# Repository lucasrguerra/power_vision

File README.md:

# Power Vision

## Descrição

O Power Vision é um projeto de código aberto destinado ao desenvolvimento de um analisador de qualidade da energia elétrica em tempo real utilizando um hardware de baixo custo com o microcontrolador ESP32-S3. Este analisador é capaz de medir e calcular uma variedade de parâmetros elétricos em sistemas monofásicos e trifásicos, fornecendo informações cruciais para análise e monitoramento de consumo de energia.

O projeto foi desenvolvido como Trabalho de Conclusão de Curso (TCC) do curso de Ciência da Computação da Universidade Federal Rural de Pernmabuco (UFRPE) e orientado pelo Prof. Dr. Abner Corrêa Barros. O projeto tem como objetivo principal a implementação de um analisador de energia elétrica de baixo custo e alta precisão, que possa ser utilizado em residências, empresas e indústrias para monitoramento e análise de consumo de energia.

## Funcionalidades

O Power Vision atualmente tem na teoria as seguintes funcionalidades:

- **Frequência (Hz)**: Medição da frequência do sistema.
- **Tensão True RMS (Vac)**: Medição precisa da tensão eficaz do sistema.
- **Corrente True RMS (A)**: Medição precisa da corrente eficaz do sistema.
- **Potência Aparente (kVA)**: Cálculo da potência aparente do sistema.
- **Distorção Harmônica Total (%)**: Avaliação da distorção harmônica no sistema.
- **Cosseno φ**: Cálculo do cosseno do ângulo de fase.
- **Fator de Potência (%)**: Determinação do fator de potência do sistema.
- **Potência Ativa (kW)**: Cálculo da potência ativa consumida pelo sistema.
- **Potência Reativa (kVAr)**: Cálculo da potência reativa do sistema.
- **Potência de Distorção (kVAD)**: Cálculo da potência de distorção do sistema.

## Limites de medição

Assim como qualquer equipamento de medição, o Power Vision possui limites de medição para cada parâmetro elétrico. Abaixo estão os limites de medição que este projeto visa alcançar:

### Frequência
O dispositivo possiu uma forma versátil de calcular a frequência, se mas o intervalo de leitura esperado é entre 45Hz e 60Hz.

### Tensão
O dispositivo é destinado a medições em sistemas residenciais, comerciais e industriais de pequeno e médio porte, para isso, o dispositivo conta com 4 níveis possíveis de tensão de fase (não confundir com tensão de linha, que é a tensão entre fases), sendo eles:

Nível 0 = 0-475Vac (Padrão 440V)  
Nível 1 = 0-440Vac (Padrão 380V)  
Nível 2 = 0-275Vac (Padrão 220V)  
Nível 3 = 0-175Vac (Padrão 127V)  

### Corrente
O dispositivo é destinado a medições em sistemas residenciais, comerciais e industriais de pequeno e médio porte, para isso, o dispositivo conta com 7 níveis possíveis de corrente, sendo eles:

Nível 0 = Até 1000A  
Nível 1 = Até 750A  
Nível 2 = Até 500A  
Nível 3 = Até 300A  
Nível 4 = Até 200A  
Nível 5 = Até 120A  
Nível 6 = Até 80A  

## Estrutura do Projeto

O projeto está organizado da seguinte forma:

- **[`src/`](./src/)**: Contém o código fonte principal do analisador de energia, que vai no Microcontrolador. (Em desenvolvimento 🛠️)

- **[`docs/`](./docs/)**: Documentação do projeto, incluindo manuais de usuário, especificações técnicas e outras informações relevantes.

- **[`theory/`](./theory/)**: Esta pasta contém implementações em Python das fórmulas utilizadas antes de serem integradas ao código principal do microcontrolador. (Sendo atualizado para a transformada Wavelet 🛠️)

- **[`boards/`](./boards/)**: Contém informações sobre as placas desenvolvidas para o projeto e os arquivos de fabricação no formato Gerber.

## Como Contribuir

Sinta-se à vontade para contribuir com o projeto! Você pode:

- Reportar problemas encontrados.
- Propor melhorias e novas funcionalidades.
- Enviar correções ou otimizações de código.
- Compartilhar suas experiências e ideias.

## Como Utilizar

Para utilizar o Power Vision, siga estas etapas:

1. Clone o repositório para o seu ambiente de desenvolvimento com o PlatformIO instalado.
2. Instale as dependências necessárias:
    (Atenção: Este projeto ainda não possui dependências)
3. Compile e carregue o código no seu ESP32-S3.
4. Monte o circuito conforme o esquemático disponível na pasta [`docs/`](./docs/).
4. Conecte o analisador de energia ao sistema que deseja analisar.
5. Inicie o analisador e visualize os resultados pela interface serial.

## Créditos

Este projeto foi criador por [Lucas Rayan](https://www.linkedin.com/in/lucasrguerra/) (vulgo "eu") e continua sendo mantido por ele.

## Agradecimentos

A minha mãe, que sempre lutou muito para que eu e minha irmã tivéssemos uma boa educação, e que sempre me apoiou em todas as minhas decisões. E que é sem dúvida a pessoa mais importante da minha vida.

Ao [Prof. Dr. Abner Corrêa Barros](https://www.linkedin.com/in/abner-barros-5b86409/), meu orientador, que sempre esteve disposto a ajudar e doar seu tempo e conhecimento para contribuir com o desenvolvimento do projeto.

A minha grande amiga e companheira de vida, [Vitória das Dores](https://www.linkedin.com/in/vitoria-das-dores/), que sempre esteve ao meu lado me apoiando e me ajudando a superar todos os desafios.

Ao meu grande amigo e grande Engenheiro Eletrônico, [João Pontes](https://www.linkedin.com/in/joão-victor-b-pontes-b37006116/), que sempre esteve disposto a ajudar e ouvir minhas ideias e dúvidas.

## Licença

Este projeto está licenciado sob a Licença MIT. Consulte o arquivo [LICENSE](./LICENSE) para obter mais detalhes.

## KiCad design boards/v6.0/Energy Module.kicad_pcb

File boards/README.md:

# Placas do projeto

## Descrição

Nesta pasta estão todos os arquivos das placas desenvolvidas para este projeto utilizando o software KiCAD. Dentre esses arquivos, estão o esquemático, o layout da placa e seus arquivos de fabricação no formato Gerber.

## Versões Disponíveis

- **[`v4.0`](./v4.0/)**: Essa é a 12ª versão da placa e no modelo SMT (Surface-Mount Technology).
- **[`v3.4`](./v3.4/)**: Essa é a 11ª versão da placa e no modelo SMT (Surface-Mount Technology).
- **[`v3.3`](./v3.3/)**: Essa é a 10ª versão da placa e no modelo THT (Through-Hole Technology).
- **[`v3.2`](./v3.2/)**: Essa é a 9ª versão da placa e no modelo THT (Through-Hole Technology).
- **[`v3.1`](./v3.1/)**: Essa é a 8ª versão da placa e no modelo THT (Through-Hole Technology).
- **[`v3.0`](./v3.0/)**: Essa é a 7ª versão da placa e no modelo THT (Through-Hole Technology).
- **[`v2.1`](./v2.1/)**: Essa é a 6ª versão da placa e no modelo THT (Through-Hole Technology).
- **[`v2.0`](./v2.0/)**: Essa é a 5ª versão da placa e no modelo THT (Through-Hole Technology).
- **[`v1.1`](./v1.1/)**: Essa é a 4ª versão da placa e no modelo THT (Through-Hole Technology).
- **[`v1.0`](./v1.0/)**: Essa é a 3ª versão da placa e no modelo THT (Through-Hole Technology).
- **[`v0.7`](./v0.7/)**: Essa é a 2ª versão da placa e no modelo SMT (Surface-Mount Technology).
- **[`v0.5`](./v0.5/)**: Essa é a 1ª versão da placa e no modelo THT (Through-Hole Technology).

## Dados das Placas

### Placa v4.0 (SMT) - 75,438mm de largura x 74,930mm de altura

Essa placa foi desenvolvida com um design mais compacto e organizado da versão anterior. Ela possui apenas 2 camadas de cobre para manter o baixo custo. Essa placa pussui ainda mais cuidado com a simetria das trilhas diferenciais para garantir o menor erro de impedância o possível nas medições. Além disso, a possui o plano terra em ambas as camadas, garantindo uma melhor dissipação de calor e reduzindo a interferência eletromagnética. Por fim, a fonte de alimentação interna foi removida, pois ela era um limitante de tensão de operação do circuito.

### Placa v3.4 (SMT) - 77,6358mm de largura x 89,3210mm de altura

Essa placa foi desenvolvida com um design mais compacto e organizado da versão anterior. Ela possui 4 camadas de cobre, tornando mínima a impedância do GND e da tensão de referência para as medições. Essa placa também possui um cuidado com a simetria das trilhas diferenciais para garantir o menor erro de impedância o possível nas medições. Além disso, a possui uma camada dedicada ao plano terra, garantindo uma melhor dissipação de calor e reduzindo a interferência eletromagnética.

### Placa v3.3 (THT) - 96,012mm de largura x 91,440mm de altura (Atual THT)

Essa placa foi desenvolvida mantendo o design compacto e organizado da versão anterior. Ela possui além dos circuitos de transimpedância, os buffers de tensão, garantindo uma maior precisão nas medições. A placa também possui resistores de 50Ω para aumentar a estabilidade dos sinais vindos dos buffers de tensão e limitar a corrente que passa pelos diodos zener de proteção. Além disso, a placa é a primeira a possuir um plano de terra, garantindo uma melhor dissipação de calor e reduzindo a interferência eletromagnética.

### Placa v3.2 (THT) - 94,448mm de largura x 92,710mm de altura

Essa placa foi desenvolvida para ser mais compacta e organizada que a anterior. Ela não usa mais os buffers de tensão, que foram substituidos pelo mesmo amplificadores operacionais, mas agora em uma configuração de transimpedância, garantiando uma maior precisão nas medições. A placa também não necessita mais do circuito de seleção do tipo de sistema elétrico, deixando essa opção para o software. Além disso, a placa possui um layout mais compacto e organizado que as anteriores.

### Placa v3.1 (THT) - 99,842mm de largura x 91,948mm de altura

Essa placa foi desenvolvida sem a necessidade da leitura das tensões de linha. Ela possui em seu esquemático as tabelas de resistores para cada nível de tensão e corrente no qual se deseja operar. Vale ressaltar que todos os resistores shunt utilizados foram recalculados para melhorar a precisão das medições e aproveitar melhor a faixa de operação do ADC do ESP32-S3, assim como, todos os sinais agora estão conectados a canais do ADC 1 do ESP32-S3, trazendo uma maior precisão as leituras. Além disso, a placa possui um layout mais compacto que as anteriores.

### Placa v3.0 (THT) - 113,284mm de largura x 98,044mm de altura

Essa placa foi desenvolvida para ser condicionar melhor os sinais de corrente e tensão, utilizando diversos buffers para isso. Ela não possui mais um circuito de seleção de níveis de corrente, operando de acordo com a resistor shunt utilizado. Ela também não possui mais um circuito de gerenciamento de bateria. Vale ressaltar que todos os resistores shunt utilizados foram recalculados para melhorar a precisão das medições e aproveitar melhor a faixa de operação do ADC do ESP32-S3. Além disso, a placa possui um layout mais compacto e organizado que as anteriores.

### Placa v2.1 (THT) - 139,700mm de largura x 116,840mm de altura

Essa placa foi desenvolvida para ser mais compacta e organizada que a anterior. Além disso, ela possui pequenas correções, como a seleção manual do nível de corrente a ser utilizado nas medições e também  a largura de cada trilha da placa, aumentando a largura de trilhas com maior corrente. Nessa placa a cor da placa também foi alterada para preto.

### Placa v2.1 (THT) - 144,780mm de largura x 101,419mm de altura

Essa placa possui um menos transformadores de potencial, mas tem agora um circuito resposável pelo gerenciamento da energia utilizada na placa, com suporte para baterias 18650 de Ion-Lítion, um seleção de níveis de corrente, sendo eles 300A e 1000A, e suporte a módulos de cartão SD. Além disso, a placa possui um layout mais organizado que as anteriores. Além disso, ela possui pequenas correções, como a adição de um diodo retificador para proteção do circuito de seleção de níveis de corrente e a correção do identificador de todos os componentes no Footprint.

### Placa v1.1 (THT) - 143,510mm de largura x 73,025mm de altura

Essa placa possui o mesmo layout da anterior. Porém, foram corrigidos os nomes dos Diodos Zener no Footprint e foi adicionado um Diodo Retificador para proteção do circuito de seleção de níveis de corrente.

### Placa v1.0 (THT) - 143,510mm de largura x 73,025mm de altura

Essa placa possui um layout mais compacto e organizado que as anteriores, além de ter a conexão entre o ESP32-S3 e o módulo de interrupção de níveis de corrente. E os níveis de corrente dessa placa são 30A e 100A, possibilitando uma leiura mais precisa e adequada ao sensor utilizado, especialmente em baixas correntes.

### Placa v0.7 (SMT) - 90,170mm de largura x 82,423mm de altura

Essa placa possui um layout mais compacto e organizado que a primeira versão. Porém, ele não possui a seleção de níveis de corrente, lendo apenas na escala de 100A.

### Placa v0.5 (THT) - 119,380mm de largura x 116,840mm de altura

Essa placa possui um layout menos compacto e organizado. Além disso, ela possui a seleção de níveis de corrente, lendo na escala de 50A e 200A.

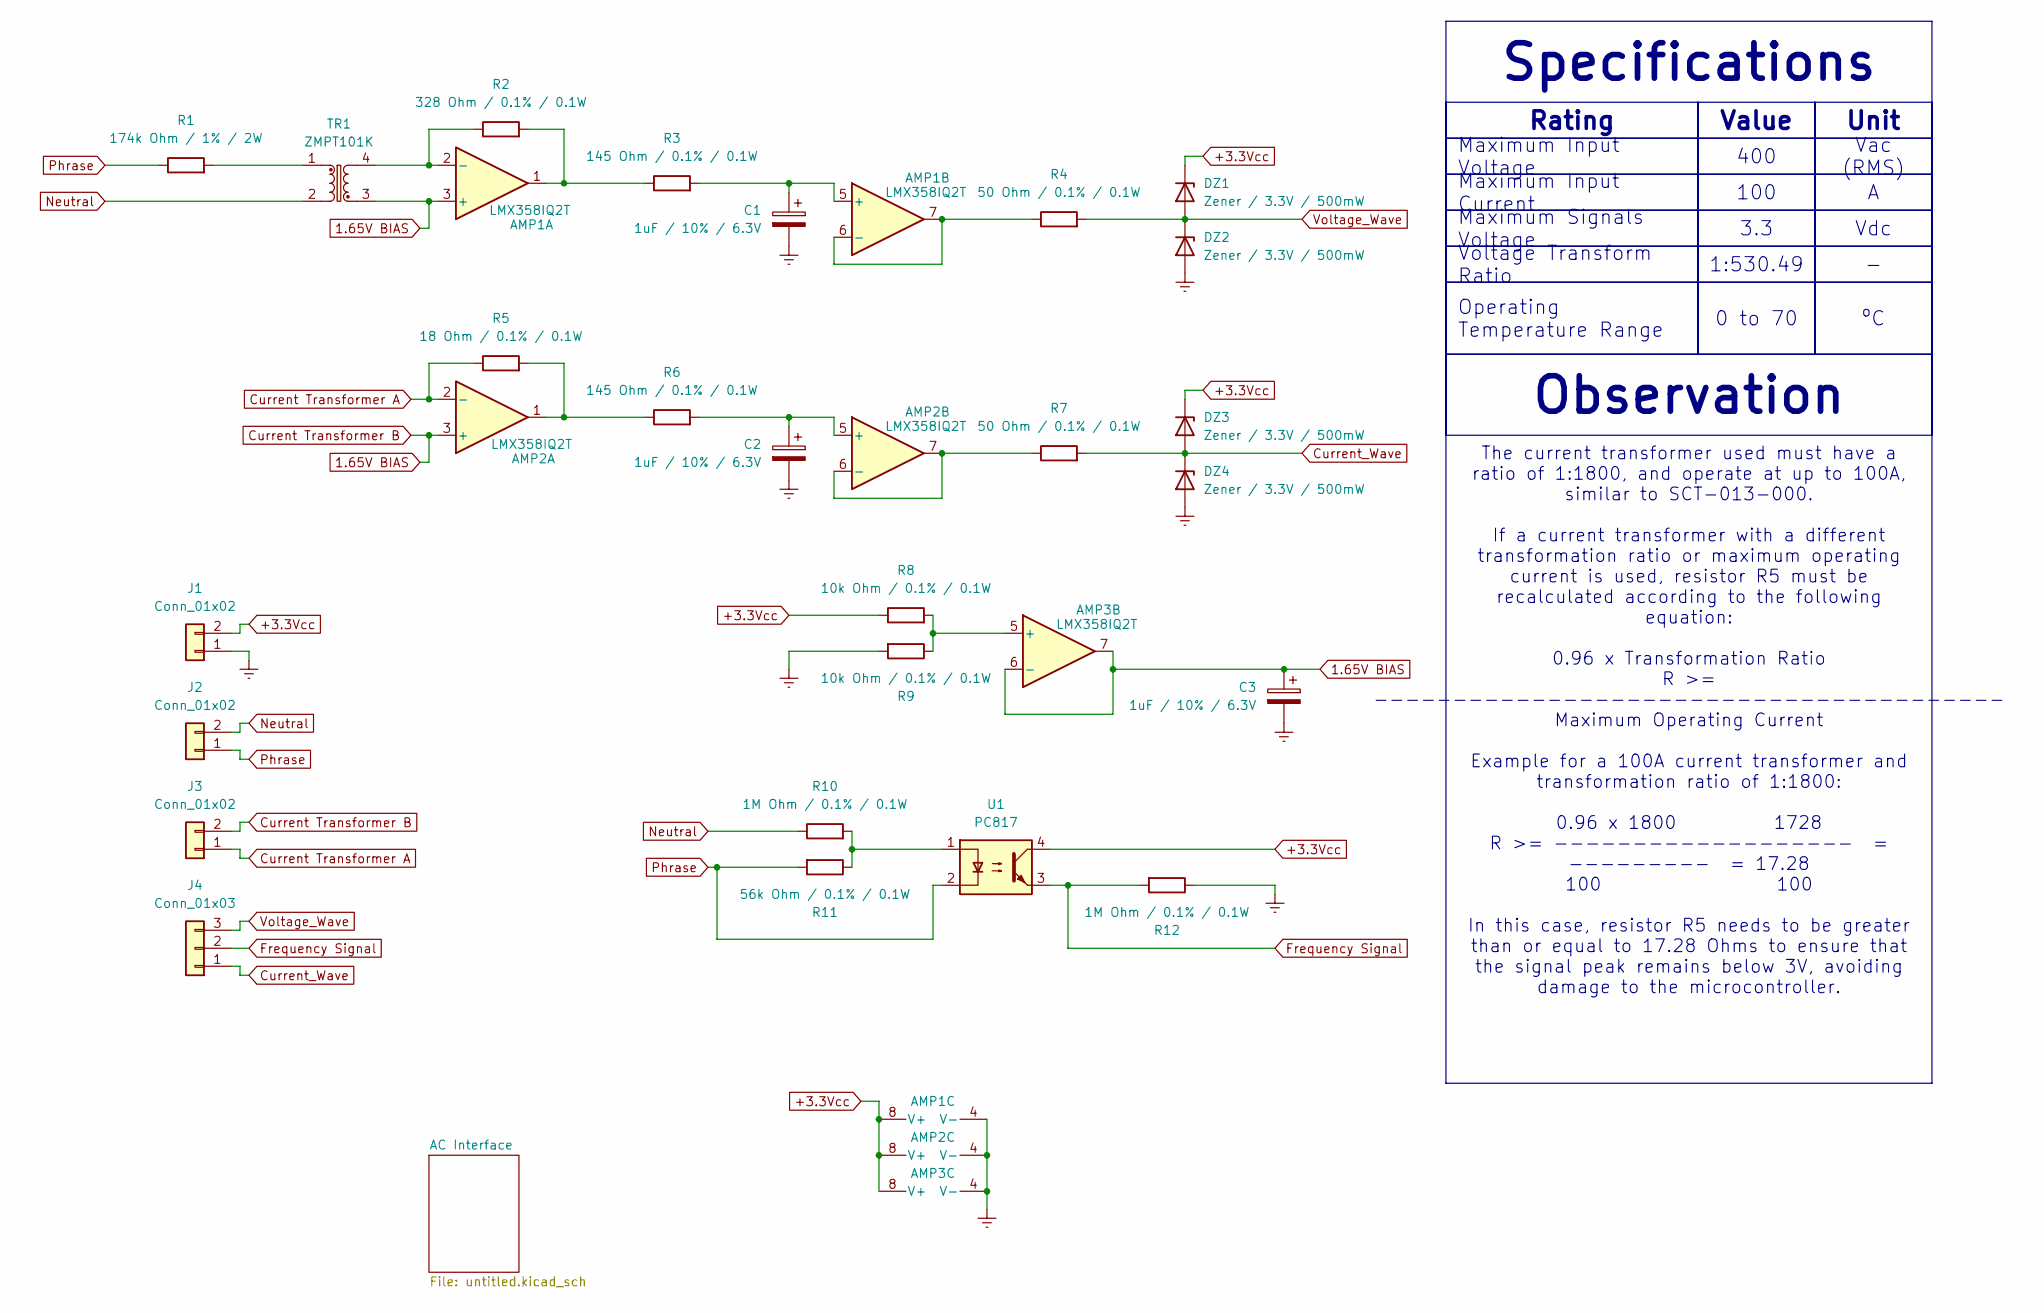
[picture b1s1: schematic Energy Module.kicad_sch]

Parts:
AMP1, AMP2, AMP3: LMX358IQ2T; DFN-8-1EP_6x5mm_P1.27mm_EP2x2mm
C1, C2, C3: 1uF / 10% / 6.3V; C_0201_0603Metric
DZ1, DZ2, DZ3, DZ4: Zener / 3.3V / 500mW; D_SOD-123
J1: Conn_01x02; PinHeader_1x02_P2.54mm_Vertical
J2, J3: Conn_01x02; PhoenixContact_MC_1,5_2-G-3.81_1x02_P3.81mm_Horizontal
J4: Conn_01x03; PinHeader_1x03_P2.54mm_Vertical
R1: 174k Ohm / 1% / 2W; R_2512_6332Metric
R2: 328 Ohm / 0.1% / 0.1W; R_0603_1608Metric
R3, R6: 145 Ohm / 0.1% / 0.1W; R_0603_1608Metric
R4, R7: 50 Ohm / 0.1% / 0.1W; R_0603_1608Metric
R5: 18 Ohm / 0.1% / 0.1W; R_0603_1608Metric
R8, R9: 10k Ohm / 0.1% / 0.1W; R_0603_1608Metric
R10, R12: 1M Ohm / 0.1% / 0.1W; R_0603_1608Metric
R11: 56k Ohm / 0.1% / 0.1W; R_0603_1608Metric
TR1: ZMPT101K; Transformer_Zeming_ZMPT101K
U1: PC817; DIP-4_W7.62mm_SMDSocket_SmallPads

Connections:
1.65V BIAS: AMP1.3 (+), AMP2.3 (+), AMP3.6 (-), AMP3.7, C3.1, J3.2, TR1.3
+3.3Vcc: AMP1.8 (V+), AMP2.8 (V+), AMP3.8 (V+), DZ1.1 (K), DZ3.1 (K), J1.2, R8.1, U1.4
Current Transformer A: AMP2.2 (-), J3.1, R5.1
Current_Wave: DZ3.2 (A), DZ4.1 (K), J4.1, R7.2
Earth: AMP1.4 (V-), AMP2.4 (V-), AMP3.4 (V-), C1.2, C2.2, C3.2, DZ2.2 (A), DZ4.2 (A), J1.1, R9.2, R12.1
Frequency Signal: J4.2, R12.2, U1.3
unnamed: AMP1.1, R2.2, R3.1
unnamed: AMP1.2 (-), R2.1, TR1.4
unnamed: AMP1.5 (+), C1.1, R3.2
unnamed: AMP1.6 (-), AMP1.7, R4.1
unnamed: AMP2.1, R5.2, R6.1
unnamed: AMP2.5 (+), C2.1, R6.2
unnamed: AMP2.6 (-), AMP2.7, R7.1
unnamed: AMP3.5 (+), R8.2, R9.1
unnamed: R1.2, TR1.1
unnamed: R10.2, R11.1, U1.1
Neutral: J2.2, R10.1, TR1.2
Phrase: J2.1, R1.1, R11.2, U1.2
Voltage_Wave: DZ1.2 (A), DZ2.1 (K), J4.3, R4.2

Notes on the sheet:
Value
Maximum Signals Voltage
1:530.49
Operating Temperature Range
The current transformer used must have a ratio of 1:1800, and operate at up to 100A, similar to SCT-013-000. If a current transformer with a different transformation ratio or maximum operating current is used, resistor R5 must be recalculated according to the following equation: 0.96 x Transformati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
Observation
Maximum Input Voltage
100
Voltage Transform Ratio
Unit
Vac (RMS)
3.3
0 to 70
400
Rating
Specifications
Vdc
Maximum Input Current

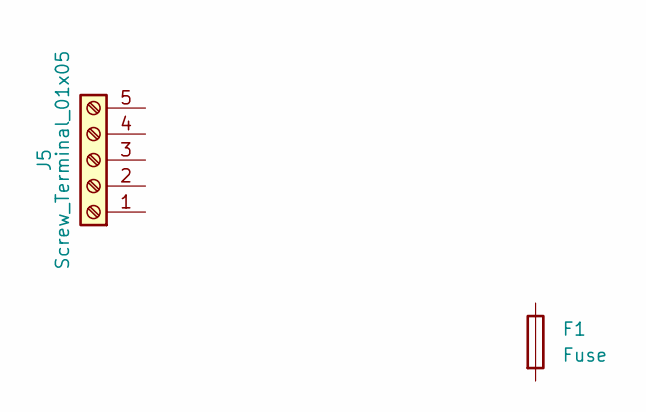
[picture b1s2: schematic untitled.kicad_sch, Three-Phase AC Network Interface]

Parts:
F1: Fuse; Fuseholder_Clip-5x20mm_Keystone_3512_Inline_P23.62x7.27mm_D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
J5: Screw_Terminal_01x05; TerminalBlock_bornier-5_P5.08mm

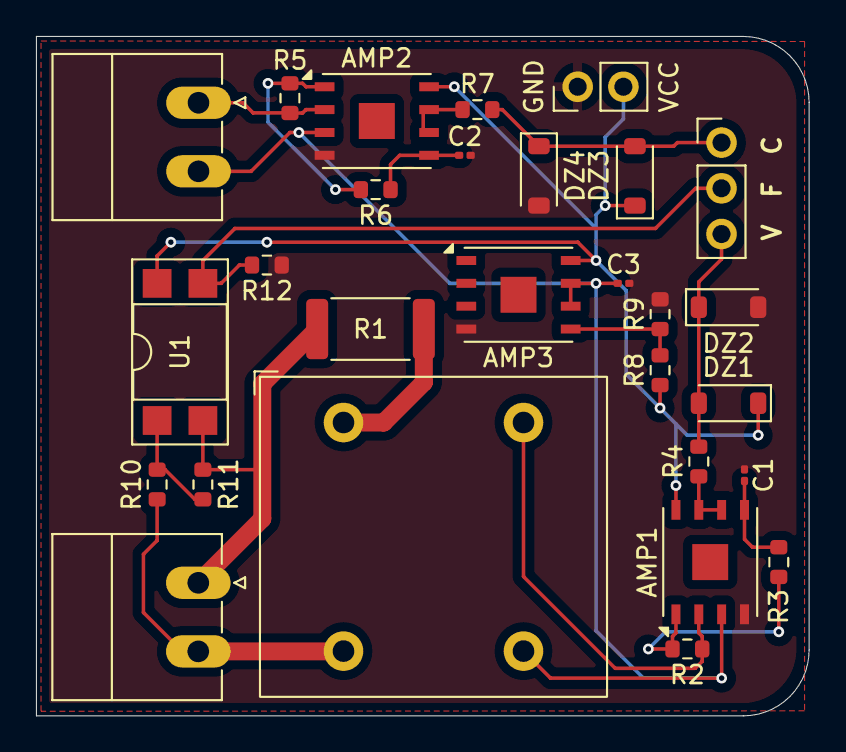
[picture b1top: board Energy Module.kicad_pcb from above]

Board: 2 copper layers, 42.9 x 37.7 mm, 28 parts (0 on the bottom side), 19 nets.

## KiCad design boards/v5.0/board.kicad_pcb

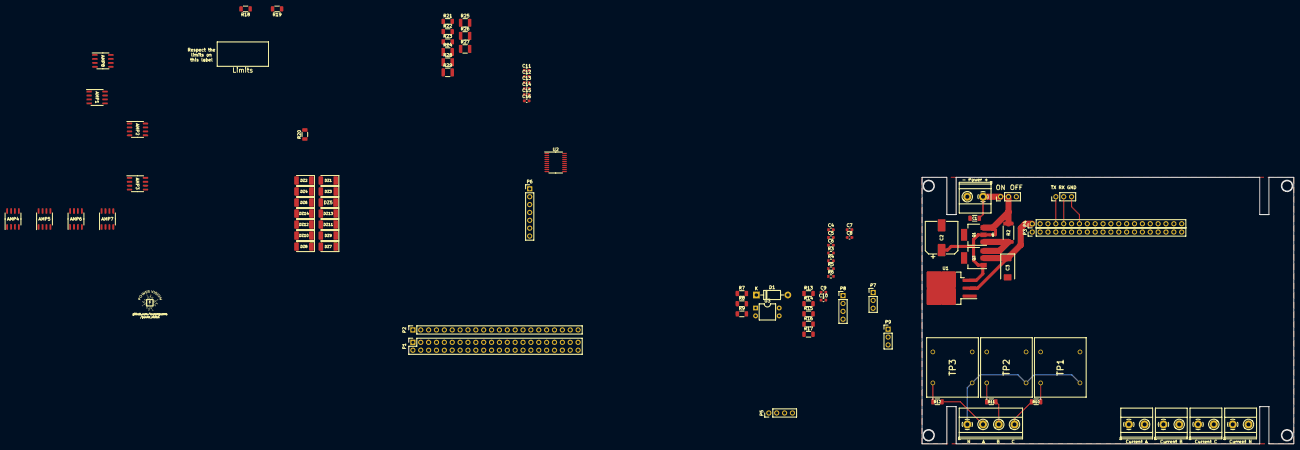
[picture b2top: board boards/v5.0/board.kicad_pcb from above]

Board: 2 copper layers, 120.0 x 86.0 mm, 93 parts (0 on the bottom side), 68 nets.

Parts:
AMP1, AMP2, AMP3, AMP4, AMP5, AMP6, AMP7, AMP8: TL082; SO-8_3.9x4.9mm_P1.27mm
C1: 100V 0.1µF; C_1206_3216Metric
C2: 50V 100µF; CP_Elec_10x10
C3: 10V 47µF; CP_EIA-7343-31_Kemet-D
C4, C5, C6, C7, C8: 10V 0.1µF; C_0603_1608Metric
C9, C10, C11, C12, C13, C14, C15, C16: 10V 0.1uF; C_0603_1608Metric
D1: 1N4007; D_DO-41_SOD81_P10.16mm_Horizontal
DZ1, DZ2, DZ3, DZ4, DZ5, DZ6, DZ7, DZ8, DZ9, DZ10, DZ11, DZ12, DZ13, DZ14: 3.3V; D_MELF
J1, J3, J4, J5, J6: Screw_Terminal_01x02; TerminalBlock_Phoenix_MKDS-1,5-2-5.08_1x02_P5.08mm_Horizont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
J2: Screw_Terminal_01x04; TerminalBlock_Phoenix_MKDS-1,5-4-5.08_1x04_P5.08mm_Horizont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
P1: Pin Socket 2.54mm 02x22; PinSocket_2x22_P2.54mm_Vertical
P2: Pin Socket 2.54mm 01x22; PinSocket_1x22_P2.54mm_Vertical
P3, P4: Conn_01x20; PinHeader_1x20_P2.54mm_Vertical
P5, P8: Pin Header; PinHeader_1x04_P2.54mm_Vertical
P6: Conn_01x07; PinHeader_1x07_P2.54mm_Vertical
P7, P9, P10: Pin Header; PinHeader_1x03_P2.54mm_Vertical
Q1, Q2: FZT948TA; SOT-223
R1: 2Ω; R_0603_1608Metric
R2: 0.2Ω; R_2512_6332Metric
R3, R4, R5, R6: 1kΩ; R_0603_1608Metric
R7, R13, R14: 10kΩ; R_1206_3216Metric
R8, R9: 1MΩ; R_1206_3216Metric
R10, R11, R12: RVolt; R_1206_3216Metric
R15, R17, R19, R21, R23: 50Ω; R_1206_3216Metric
R16, R18, R20: 430Ω; R_1206_3216Metric
R22: Rcurr; R_1206_3216Metric
R24, R26, R28: Rcurr; R_1210_3225Metric
R25, R27, R29: 50Ω; R_1210_3225Metric
SW1: SS-12D00G 4mm; PinHeader_1x03_P2.54mm_Vertical
TP1, TP2, TP3: ZMPT101B; XFMR_ZMPT101B
U1: LD1086#50; TO-263-3_TabPin2
U2: TXS0108EPW; TSSOP-20_4.4x6.5mm_P0.65mm
U3: PC817; DIP-4_W7.62mm

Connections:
/Microcomputer/3.3V: C4.1, C6.1, C7.1, DZ2.1 (K), DZ3.1 (K), DZ5.1 (K), DZ7.1 (K), DZ9.1 (K), DZ11.1 (K), DZ13.1 (K), P1.1, P1.2, P1.43, P1.44, P3.1, P3.9, R5.2, R6.1, R13.1, U2.19 (VCCB), U3.4
/Microcomputer/5V: AMP1.8 (V+), AMP2.8 (V+), AMP3.8 (V+), AMP4.8 (V+), AMP5.8 (V+), AMP6.8 (V+), AMP7.8 (V+), AMP8.8 (V+), C3.1, C5.1, C8.1, P1.21, P1.24, P4.1, P4.2, P5.3, P6.6, Q2.2 (C), R3.2, R4.1, U1.2 (OUT), U2.2 (VCCA), U2.10 (OE)
/Microcomputer/I2C SCL_1: P3.3, P5.2
/Microcomputer/I2C SDA_1: P3.2, P5.1
/Microcomputer/RX_0: P4.5, P10.2
/Microcomputer/RX_3: P3.14, U2.1 (A1)
/Microcomputer/SPI CLK: P3.12, P6.3
/Microcomputer/SPI CS: P4.12, P6.2
/Microcomputer/SPI DC: P4.13, P6.1
/Microcomputer/SPI MISO: P3.11, P6.4
/Microcomputer/SPI MOSI: P3.10, P6.5
/Microcomputer/TX_0: P4.4, P10.1
/Microcomputer/TX_3: P4.14, U2.3 (A2)
/Microcontroller/ADC1_0: DZ1.1 (K), DZ2.2 (A), P2.4, P7.1, R17.2
/Microcontroller/ADC1_1: DZ3.2 (A), DZ4.1 (K), P2.5, P7.2, R19.2
/Microcontroller/ADC1_2: DZ5.2 (A), DZ6.1 (K), P1.13, P7.3, R21.2
/Microcontroller/ADC1_3: DZ7.2 (A), DZ8.1 (K), P1.4, P1.32, P8.1, R23.2
/Microcontroller/ADC1_4: DZ11.2 (A), DZ12.1 (K), P1.5, P8.3, R27.2
/Microcontroller/ADC1_5: DZ9.2 (A), DZ10.1 (K), P1.6, P8.2, R25.2
/Microcontroller/ADC1_6: DZ13.2 (A), DZ14.1 (K), P1.7, P8.4, R29.2
/Microcontroller/GPIO_17: P1.8, R9.1, U3.3
/Microcontroller/I2C SCL: R4.2, U2.9 (A8)
/Microcontroller/I2C SDA: R3.1, U2.8 (A7)
/Microcontroller/I2C_SCL: P1.15, P1.30, R6.2, U2.12 (B8)
/Microcontroller/I2C_SDA: P1.12, P1.33, R5.1, U2.13 (B7)
/Microcontroller/RESET: P1.3, P1.42
/Microcontroller/RX_0: P2.3, P9.2
/Microcontroller/RX_1: P1.11, P1.34, U2.18 (B2)
/Microcontroller/TX_0: P2.2, P9.1
/Microcontroller/TX_1: P1.10, P1.35, U2.20 (B1)
/Power/IN+: C1.1, J1.1, SW1.1 (C)
/Signals Acquisition/Line A: D1.1 (K), J2.4, R10.2
/Signals Acquisition/Line B: J2.3, R11.2
/Signals Acquisition/Line C: J2.2, R12.2
/Signals Acquisition/Neutral: J2.1, R7.2, TP1.2, TP2.2, TP3.2, U3.1
/Signals Acquisition/PT A-1: AMP1.3 (+), AMP2.3 (+), AMP3.3 (+), AMP4.3 (+), AMP5.3 (+), AMP6.3 (+), AMP7.3 (+), C9.1, J3.1, J4.2, J5.2, J6.2, R15.1, TP1.3, TP2.3, TP3.3
/Signals Acquisition/PT A-2: AMP1.2 (-), R16.1, TP1.4
/Signals Acquisition/PT B-2: AMP2.2 (-), R18.1, TP2.4
/Signals Acquisition/PT C-2: AMP3.2 (-), R20.1, TP3.4
/Signals Conditioning/CT A-2: AMP4.2 (-), J3.2, R22.2
/Signals Conditioning/CT B-2: AMP5.2 (-), J4.1, R24.2
/Signals Conditioning/CT C-2: AMP6.2 (-), J5.1, R26.2
/Signals Conditioning/CT N-2: AMP7.2 (-), J6.1, R28.2
Earth: AMP1.4 (V-), AMP2.4 (V-), AMP3.4 (V-), AMP4.4 (V-), AMP5.4 (V-), AMP6.4 (V-), AMP7.4 (V-), AMP8.4 (V-), C1.2, C2.2, C3.2, C4.2, C5.2, C6.2, C7.2, C8.2, C9.2, C10.2, C11.2, C12.2, C13.2, C14.2, C15.2, C16.2, DZ1.2 (A), DZ4.2 (A), DZ6.2 (A), DZ8.2 (A), DZ10.2 (A), DZ12.2 (A), DZ14.2 (A), J1.2, P1.22, P1.23, P2.21, P2.22, P3.5, P3.13, P3.20, P4.3, P4.7, P4.10, P4.15, P4.17, P5.4, P6.7, P9.3, P10.3, R9.2, R14.1, SW1.3 (A), U1.1 (ADJ/GND), U2.11 (GND)
unnamed: AMP1.1, AMP1.5 (+), C10.1, R16.2
unnamed: AMP1.6 (-), AMP1.7, R17.1
unnamed: AMP2.1, AMP2.5 (+), C11.1, R18.2
unnamed: AMP2.6 (-), AMP2.7, R19.1
unnamed: AMP3.1, AMP3.5 (+), C12.1, R20.2
unnamed: AMP3.6 (-), AMP3.7, R21.1
unnamed: AMP4.1, AMP4.5 (+), C13.1, R22.1
unnamed: AMP4.6 (-), AMP4.7, R23.1
unnamed: AMP5.1, AMP5.5 (+), C14.1, R24.1
unnamed: AMP5.6 (-), AMP5.7, R25.1
unnamed: AMP6.1, AMP6.5 (+), C15.1, R26.1
unnamed: AMP6.6 (-), AMP6.7, R27.1
unnamed: AMP7.1, AMP7.5 (+), C16.1, R28.1
unnamed: AMP7.6 (-), AMP7.7, R29.1
unnamed: AMP8.3 (+), R13.2, R14.2
unnamed: AMP8.1, AMP8.2 (-), R15.2
unnamed: D1.2 (A), R8.2
unnamed: Q1.1 (B), Q2.3 (E), R2.2
unnamed: C2.1, Q1.2 (C), Q2.1 (B), R1.2, U1.3 (IN)
unnamed: Q1.3 (E), R1.1, R2.1, SW1.2 (B)
unnamed: R7.1, R8.1, U3.2
unnamed: R10.1, TP1.1
unnamed: R11.1, TP2.1
unnamed: R12.1, TP3.1

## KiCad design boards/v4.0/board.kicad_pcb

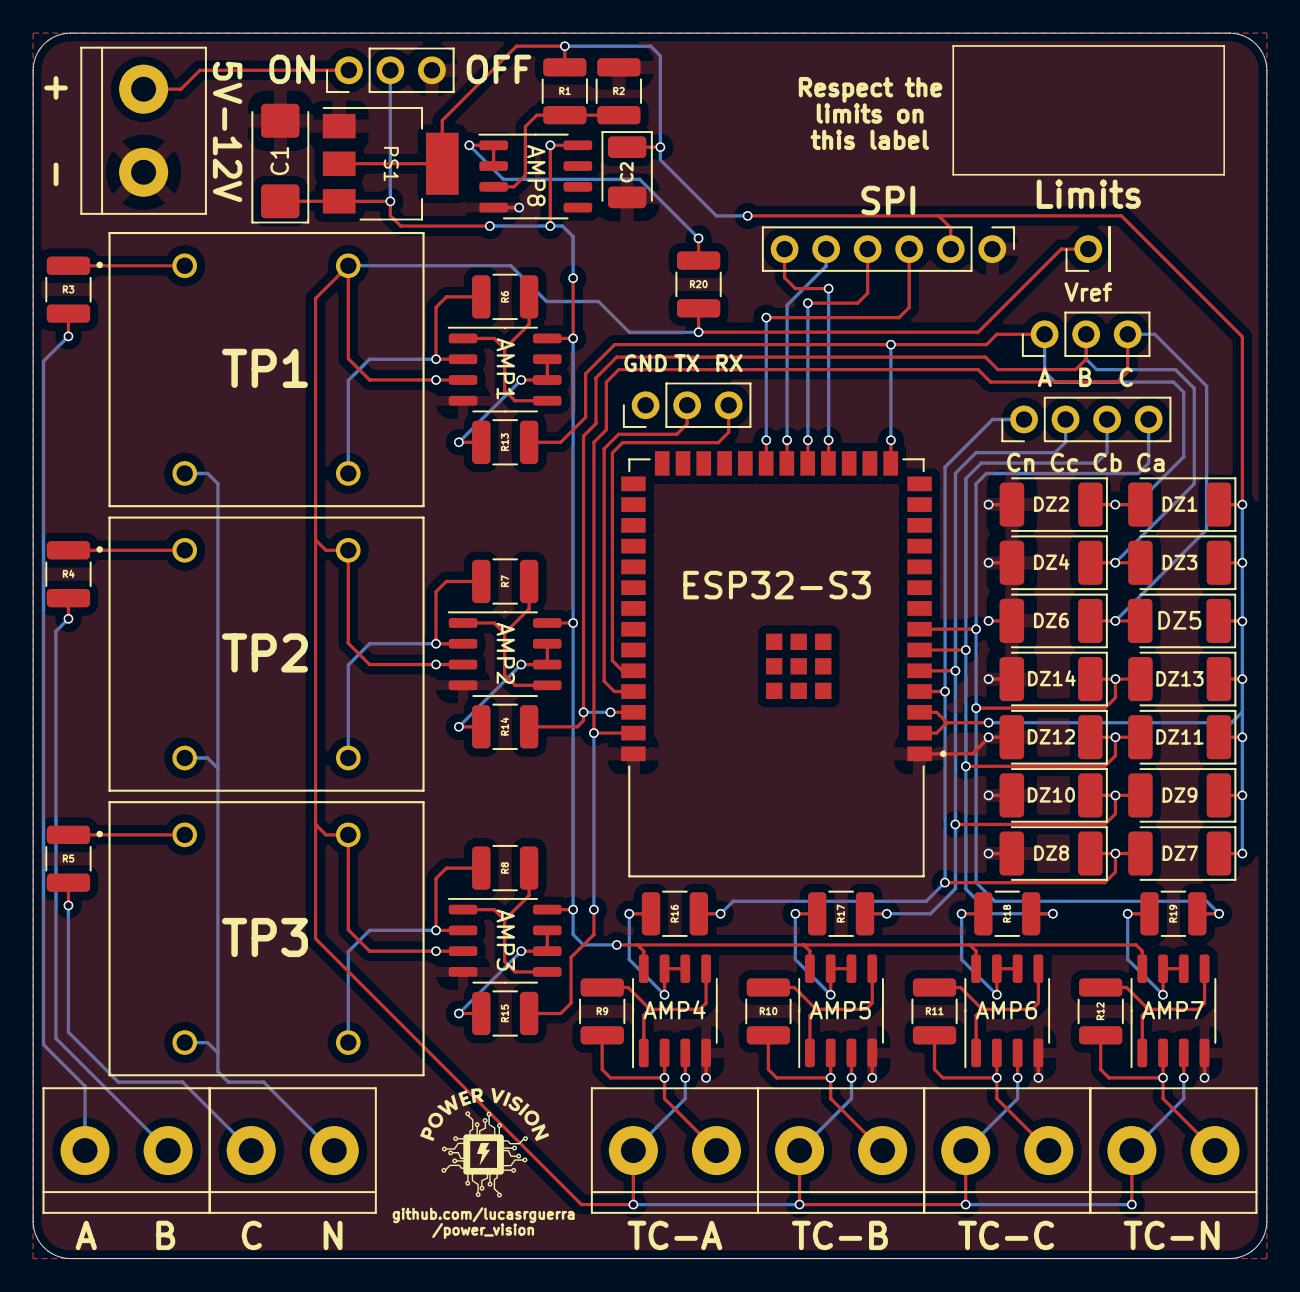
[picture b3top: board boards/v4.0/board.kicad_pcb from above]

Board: 2 copper layers, 75.4 x 74.9 mm, 62 parts (0 on the bottom side), 48 nets.

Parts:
AMP1, AMP2, AMP3, AMP4, AMP5, AMP6, AMP7, AMP8: TL082; SO-8_3.9x4.9mm_P1.27mm
C1: 25V 47µF; CP_EIA-6032-20_AVX-F
C2: 10V 100µF; CP_EIA-3528-15_AVX-H
DZ1, DZ2, DZ3, DZ4, DZ5, DZ6, DZ7, DZ8, DZ9, DZ10, DZ11, DZ12, DZ13, DZ14: 3.3V; D_MELF
J1, J2, J3, J4, J5, J6, J7: KF301-2P; TerminalBlock_bornier-2_P5.08mm
MCU1: ESP32-S3-WROOM-1-N16R8; XCVR_ESP32-S3-WROOM-2-N32R8V
P1, P4: Pin Header; PinHeader_1x03_P2.54mm_Vertical
P2: Pin Header; PinHeader_1x01_P2.54mm_Vertical
P3: Pin Header; PinHeader_1x04_P2.54mm_Vertical
P5: Pin Header; PinHeader_1x06_P2.54mm_Vertical
PS1: AMS1117-3.3; SOT-223-3_TabPin2
R1, R2: 10kΩ; R_1210_3225Metric
R3, R4, R5: RPvolt; R_1210_3225Metric
R6, R7, R8: 430Ω; R_1210_3225Metric
R9, R10, R11, R12: Rcurr; R_1210_3225Metric
R13, R14, R15, R16, R17, R18, R19, R20: 50Ω; R_1210_3225Metric
SW1: SS-12D00G 4mm; PinHeader_1x03_P2.54mm_Vertical
TP1, TP2, TP3: ZMPT101B; XFMR_ZMPT101B

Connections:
5V-12V: J1.1, SW1.1 (C)
CLK: MCU1.20 (IO12), P5.5
CS: MCU1.18 (IO10), P5.6
Current A: DZ7.2 (A), DZ8.1 (K), MCU1.4 (IO4), P3.1, R16.1
Current B: DZ9.2 (A), DZ10.1 (K), MCU1.5 (IO5), P3.2, R17.1
Current C: DZ11.2 (A), DZ12.1 (K), MCU1.6 (IO6), P3.3, R18.1
Current N: DZ13.2 (A), DZ14.1 (K), MCU1.7 (IO7), P3.4, R19.1
GND: AMP1.4 (V-), AMP2.4 (V-), AMP3.4 (V-), AMP4.4 (V-), AMP5.4 (V-), AMP6.4 (V-), AMP7.4 (V-), AMP8.4 (V-), C1.2, C2.2, DZ2.2 (A), DZ4.2 (A), DZ6.2 (A), DZ8.2 (A), DZ10.2 (A), DZ12.2 (A), DZ14.2 (A), J1.2, MCU1.1 (GND), MCU1.40 (GND__1), P1.1, P5.1, PS1.1 (GND), R2.2, SW1.3 (A)
Line A: J3.1, R3.2
Line B: J3.2, R4.2
Line C: J2.1, R5.2
MISO: MCU1.21 (IO13), P5.3
MOSI: MCU1.19 (IO11), P5.4
unnamed: AMP1.1, AMP1.5 (+), R6.2
unnamed: AMP1.6 (-), AMP1.7, R13.2
unnamed: AMP2.1, AMP2.5 (+), R7.2
unnamed: AMP2.6 (-), AMP2.7, R14.2
unnamed: AMP3.1, AMP3.5 (+), R8.2
unnamed: AMP3.6 (-), AMP3.7, R15.2
unnamed: AMP4.1, AMP4.5 (+), R9.1
unnamed: AMP4.6 (-), AMP4.7, R16.2
unnamed: AMP5.1, AMP5.5 (+), R10.1
unnamed: AMP5.6 (-), AMP5.7, R17.2
unnamed: AMP6.1, AMP6.5 (+), R11.1
unnamed: AMP6.6 (-), AMP6.7, R18.2
unnamed: AMP7.1, AMP7.5 (+), R12.1
unnamed: AMP7.6 (-), AMP7.7, R19.2
unnamed: AMP8.1, AMP8.2 (-), R20.2
unnamed: R3.1, TP1.1
unnamed: R4.1, TP2.1
unnamed: R5.1, TP3.1
Neutral: J2.2, TP1.2, TP2.2, TP3.2
TC A-1: AMP1.3 (+), AMP2.3 (+), AMP3.3 (+), AMP4.3 (+), AMP5.3 (+), AMP6.3 (+), AMP7.3 (+), J4.1, J5.1, J6.1, J7.1, P2.1, R20.1, TP1.4, TP2.4, TP3.4
TC A-2: AMP4.2 (-), J4.2, R9.2
TC B-2: AMP5.2 (-), J5.2, R10.2
TC C-2: AMP6.2 (-), J6.2, R11.2
TC N-2: AMP7.2 (-), J7.2, R12.2
TP A-1: AMP1.2 (-), R6.1, TP1.3
TP B-1: AMP2.2 (-), R7.1, TP2.3
TP C-1: AMP3.2 (-), R8.1, TP3.3
UART RX: MCU1.36 (RXD0), P1.3
UART TX: MCU1.37 (TXD0), P1.2
V1.65: AMP8.3 (+), R1.2, R2.1
Vcc: C2.1, DZ1.1 (K), DZ3.1 (K), DZ5.1 (K), DZ7.1 (K), DZ9.1 (K), DZ11.1 (K), DZ13.1 (K), MCU1.2 (3V3), MCU1.3 (EN), P5.2, PS1.2 (VO), R1.1
Vin: AMP1.8 (V+), AMP2.8 (V+), AMP3.8 (V+), AMP4.8 (V+), AMP5.8 (V+), AMP6.8 (V+), AMP7.8 (V+), AMP8.8 (V+), C1.1, PS1.3 (VI), SW1.2 (B)
Wave A: DZ1.2 (A), DZ2.1 (K), MCU1.15 (IO3), P4.1, R13.1
Wave B: DZ3.2 (A), DZ4.1 (K), MCU1.38 (IO2), P4.2, R14.1
Wave C: DZ5.2 (A), DZ6.1 (K), MCU1.39 (IO1), P4.3, R15.1

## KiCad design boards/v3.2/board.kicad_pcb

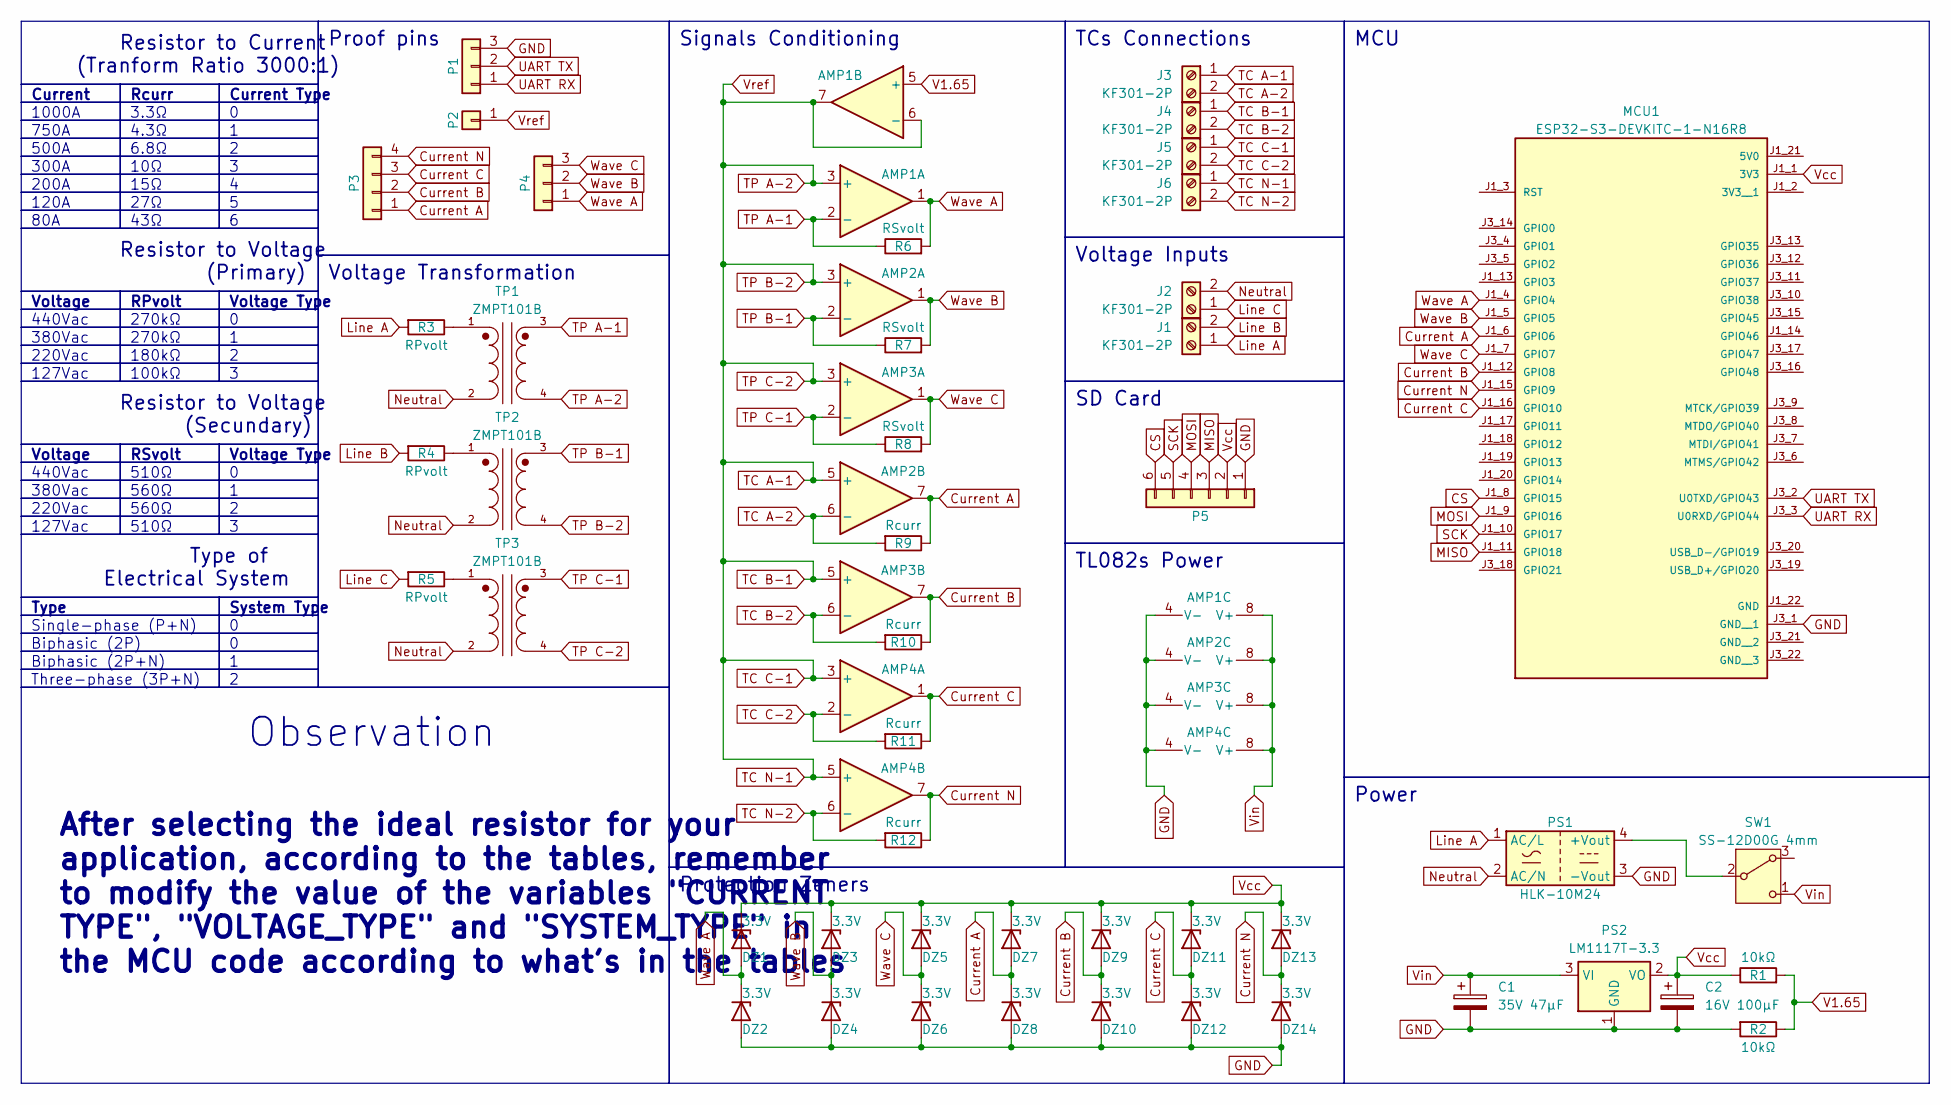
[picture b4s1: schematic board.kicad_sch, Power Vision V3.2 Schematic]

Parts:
AMP1, AMP2, AMP3, AMP4: TL082; DIP-8_W7.62mm_Socket
C1: 35V 47µF; CP_Radial_Tantal_D6.0mm_P2.50mm
C2: 16V 100µF; CP_Radial_Tantal_D5.0mm_P2.50mm
DZ1, DZ2, DZ3, DZ4, DZ5, DZ6, DZ7, DZ8, DZ9, DZ10, DZ11, DZ12, DZ13, DZ14: 3.3V; D_DO-34_SOD68_P7.62mm_Horizontal
J1, J2, J3, J4, J5, J6: KF301-2P; TerminalBlock_bornier-2_P5.08mm
MCU1: ESP32-S3-DEVKITC-1-N16R8; XCVR_ESP32-S3-DEVKITC-1-N8R2; PARTREV V1
P1, P4: Pin Header; PinHeader_1x03_P2.54mm_Vertical
P2: Pin Header; PinHeader_1x01_P2.54mm_Vertical
P3: Pin Header; PinHeader_1x04_P2.54mm_Vertical
P5: Pin Header; PinHeader_1x06_P2.54mm_Vertical
PS1: HLK-10M24; Converter_ACDC_HiLink_HLK-5Mxx
PS2: LM1117T-3.3; TO-220-3_Vertical
R1, R2: 10kΩ; R_Axial_DIN0207_L6.3mm_D2.5mm_P10.16mm_Horizontal
R3, R4, R5: RPvolt; R_Axial_DIN0207_L6.3mm_D2.5mm_P10.16mm_Horizontal
R6, R7, R8: RSvolt; R_Axial_DIN0207_L6.3mm_D2.5mm_P10.16mm_Horizontal
R9, R10, R11, R12: Rcurr; R_Axial_DIN0207_L6.3mm_D2.5mm_P10.16mm_Horizontal
SW1: SS-12D00G 4mm; PinHeader_1x03_P2.54mm_Vertical
TP1, TP2, TP3: ZMPT101B; XFMR_ZMPT101B; PARTREV NA

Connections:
CS: MCU1.J1_8 (GPIO15), P5.6
Current A: AMP2.7, DZ7.2 (A), DZ8.1 (K), MCU1.J1_6 (GPIO6), P3.1, R9.1
Current B: AMP3.7, DZ9.2 (A), DZ10.1 (K), MCU1.J1_12 (GPIO8), P3.2, R10.1
Current C: AMP4.1, DZ11.2 (A), DZ12.1 (K), MCU1.J1_16 (GPIO10), P3.3, R11.1
Current N: AMP4.7, DZ13.2 (A), DZ14.1 (K), MCU1.J1_15 (GPIO9), P3.4, R12.1
GND: AMP1.4 (V-), AMP2.4 (V-), AMP3.4 (V-), AMP4.4 (V-), C1.2, C2.2, DZ2.2 (A), DZ4.2 (A), DZ6.2 (A), DZ8.2 (A), DZ10.2 (A), DZ12.2 (A), DZ14.2 (A), MCU1.J3_1 (GND__1), P1.3, P5.1, PS1.3 (-Vout), PS2.1 (GND), R2.2
Line A: J1.1, PS1.1 (AC/L), R3.2
Line B: J1.2, R4.2
Line C: J2.1, R5.2
MISO: MCU1.J1_11 (GPIO18), P5.3
MOSI: MCU1.J1_9 (GPIO16), P5.4
unnamed: PS1.4 (+Vout), SW1.2 (B)
unnamed: R3.1, TP1.1
unnamed: R4.1, TP2.1
unnamed: R5.1, TP3.1
Neutral: J2.2, PS1.2 (AC/N), TP1.2, TP2.2, TP3.2
SCK: MCU1.J1_10 (GPIO17), P5.5
TC A-1: AMP1.3 (+), AMP1.6 (-), AMP1.7, AMP2.3 (+), AMP2.5 (+), AMP3.3 (+), AMP3.5 (+), AMP4.3 (+), AMP4.5 (+), J3.1, J4.1, J5.1, J6.1, P2.1, TP1.4, TP2.4, TP3.4
TC A-2: AMP2.6 (-), J3.2, R9.2
TC B-2: AMP3.6 (-), J4.2, R10.2
TC C-2: AMP4.2 (-), J5.2, R11.2
TC N-2: AMP4.6 (-), J6.2, R12.2
TP A-1: AMP1.2 (-), R6.1, TP1.3
TP B-1: AMP2.2 (-), R7.1, TP2.3
TP C-1: AMP3.2 (-), R8.1, TP3.3
UART RX: MCU1.J3_3 (U0RXD/GPIO44), P1.1
UART TX: MCU1.J3_2 (U0TXD/GPIO43), P1.2
V1.65: AMP1.5 (+), R1.2, R2.1
Vcc: C2.1, DZ1.1 (K), DZ3.1 (K), DZ5.1 (K), DZ7.1 (K), DZ9.1 (K), DZ11.1 (K), DZ13.1 (K), MCU1.J1_1 (3V3), P5.2, PS2.2 (VO), R1.1
Vin: AMP1.8 (V+), AMP2.8 (V+), AMP3.8 (V+), AMP4.8 (V+), C1.1, PS2.3 (VI), SW1.1 (C)
Wave A: AMP1.1, DZ1.2 (A), DZ2.1 (K), MCU1.J1_4 (GPIO4), P4.1, R6.2
Wave B: AMP2.1, DZ3.2 (A), DZ4.1 (K), MCU1.J1_5 (GPIO5), P4.2, R7.2
Wave C: AMP3.1, DZ5.2 (A), DZ6.1 (K), MCU1.J1_7 (GPIO7), P4.3, R8.2

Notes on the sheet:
43Ω
Resistor to Voltage (Secundary)
Type
15Ω
220Vac
380Vac
Biphasic (2P)
560Ω
RSvolt
500A
Type of Electrical System
Voltage Type
Current
300A
MCU
4.3Ω
750A
440Vac
6.8Ω
RPvolt
Power
270kΩ
100kΩ
Voltage
Voltage Inputs
System Type
27Ω
10Ω
Resistor to Voltage (Primary)
After selecting the ideal resistor for your application, according to the tables, remember to modify the value of the variables "CURRENT TYPE", "VOLTAGE_TYPE" and "SYSTEM_TYPE" in the MCU code according to what's in the tables
120A
Protection Zeners
127Vac
TL082s Power
180kΩ
Signals Conditioning
1000A
Current Type
Voltage Transformation
200A

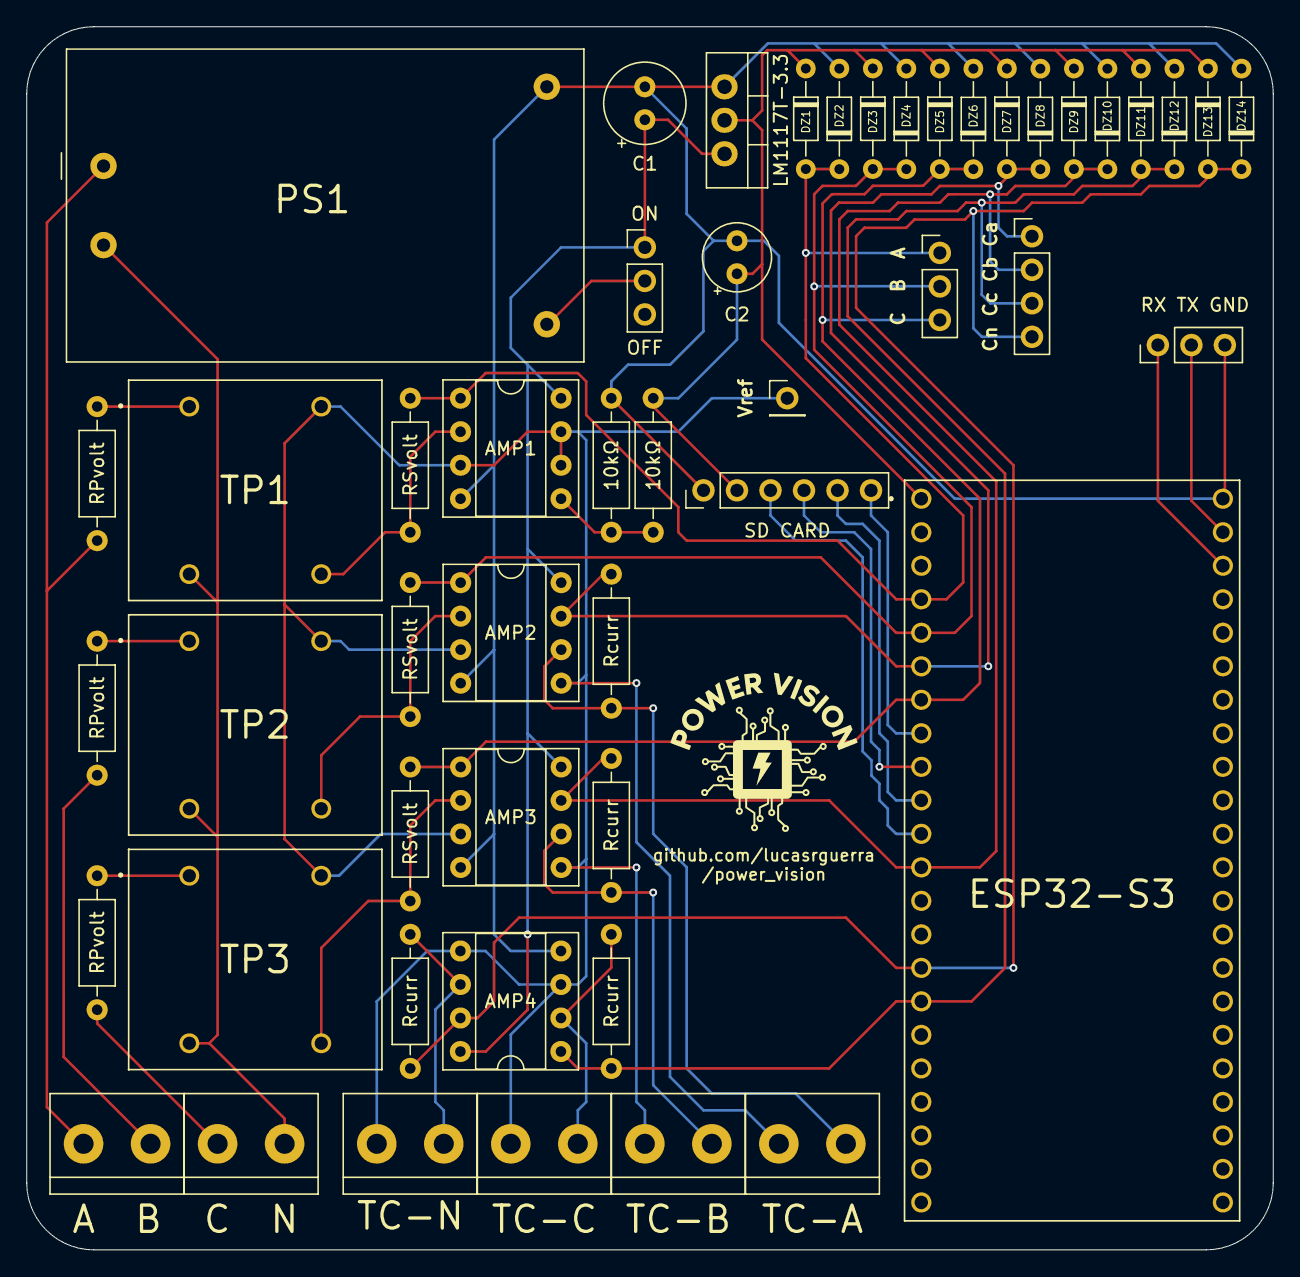
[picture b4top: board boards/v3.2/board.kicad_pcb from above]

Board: 2 copper layers, 94.5 x 92.7 mm, 50 parts (0 on the bottom side), 33 nets.
